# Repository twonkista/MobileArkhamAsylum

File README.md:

The Mobile Arkham Asylum is a hardware project that combines embedded systems with power electronics to make a literal cage for my phone so I can physically stay away from my phone. 

Such times inlude:
- study times
- bed

Features:
- 2 hour mode button (to lock for 2 hours)
- 8 hour mode button (to lock for 8 hours)
- I2C display (for time left and a generic clock)
- toggle button (to toggle the aformentioned stuff)

What I will bring:
- KiCad Schematic + footprint (done my g) (further improvements will be made like removing all voltage calculators im just gonna buy a voltimeter or steal one from someone)
- Arduino code (code done)
- Fusion 360 model

Full Plan + BOM

[BOM](https://docs.google.com/document/d/e/2PACX-1vQ0ssNzyhJEF3FpFiAyLGEXaUKHkRYoLOrRBAidYV5ManKBPaF_fq7NoqSav6IvK6zJQknT9mqp2-qP/pub) 

Picture of PCB (Render)

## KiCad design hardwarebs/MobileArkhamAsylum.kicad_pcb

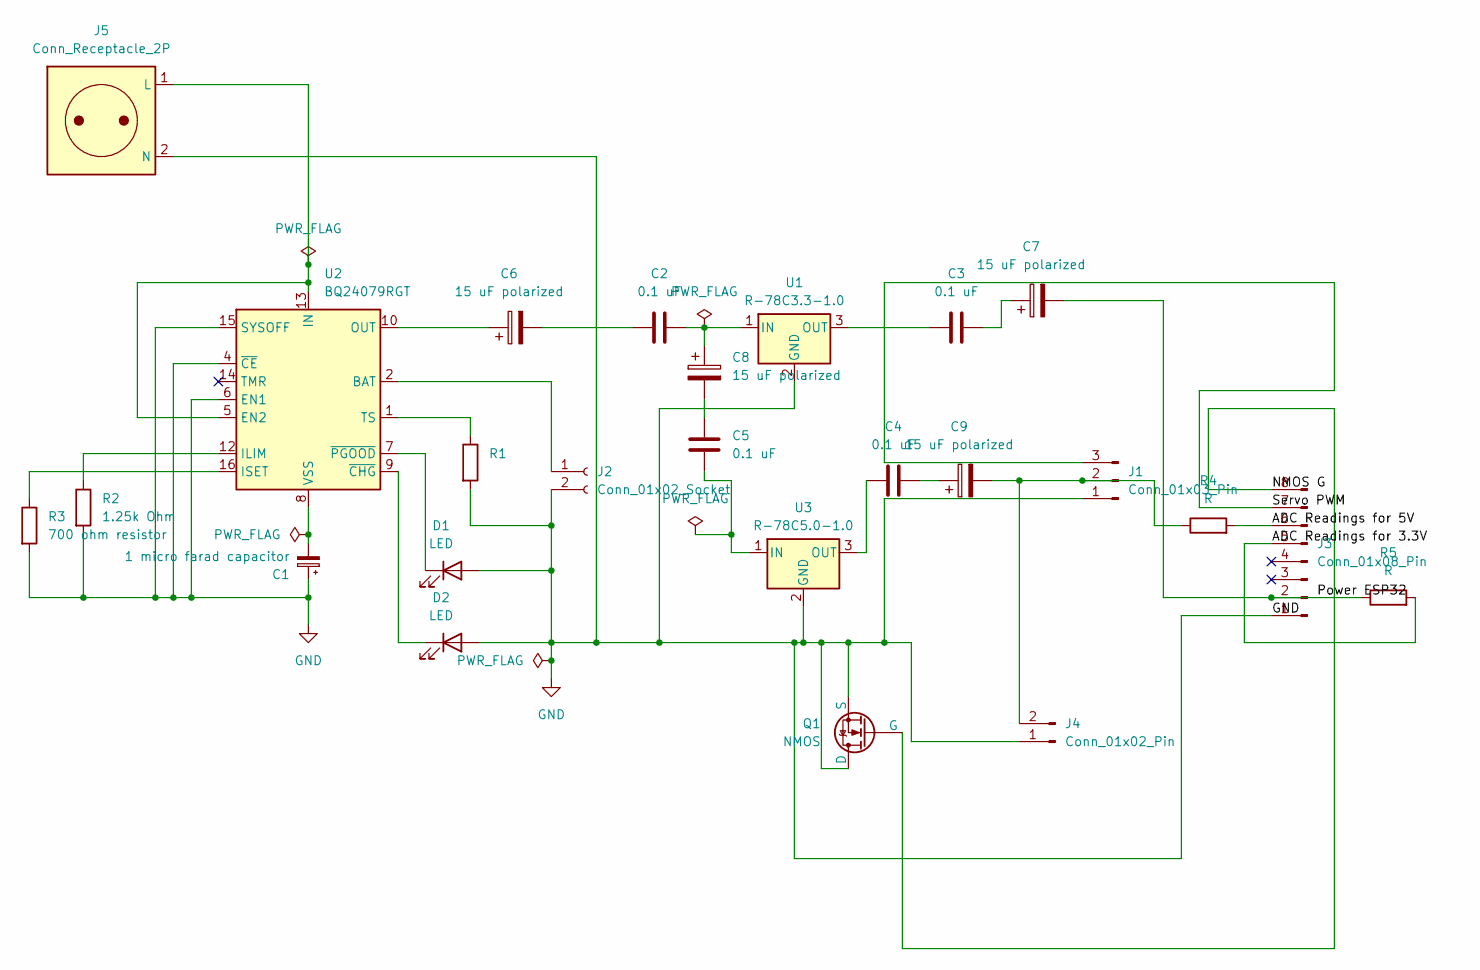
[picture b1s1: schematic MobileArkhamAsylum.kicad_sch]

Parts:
C1: 1 micro farad capacitor; CP_Radial_D5.0mm_P2.00mm
C2, C3, C4, C5: 0.1 uF; CP_Radial_D5.0mm_P2.50mm
C6, C7, C8, C9: 15 uF polarized; CP_Radial_D6.3mm_P2.50mm
D1, D2: LED; LED_D5.0mm
J1: Conn_01x03_Pin; PinHeader_1x03_P1.27mm_Vertical
J2: Conn_01x02_Socket; PinSocket_1x02_P1.27mm_Vertical
J3: Conn_01x08_Pin; PinHeader_1x08_P1.27mm_Vertical
J4: Conn_01x02_Pin; PinHeader_1x02_P1.27mm_Vertical
J5: Conn_Receptacle_2P; BarrelJack_CUI_PJ-063AH_Horizontal
Q1: NMOS; SOT-23
R1: 10k Ohms; R_Axial_DIN0204_L3.6mm_D1.6mm_P7.62mm_Horizontal
R2: 1.25k Ohm; R_Axial_DIN0204_L3.6mm_D1.6mm_P7.62mm_Horizontal
R3: 700 ohm resistor; R_Axial_DIN0204_L3.6mm_D1.6mm_P7.62mm_Horizontal
R4, R5: R; R_Axial_DIN0414_L11.9mm_D4.5mm_P5.08mm_Vertical
U1: R-78C3.3-1.0; Converter_DCDC_RECOM_R-78E-0.5_THT
U2: BQ24079RGT; VQFN-16-1EP_3x3mm_P0.5mm_EP1.6x1.6mm
U3: R-78C5.0-1.0; Converter_DCDC_RECOM_R-78E-0.5_THT

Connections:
/ADC Readings for 3.3V: J3.5, R5.2
/ADC Readings for 5V: J3.6, R4.2
/NMOS G: J3.8, Q1.2 (G)
/Power ESP32: C7.2, J3.2, R5.1
/Servo PWM: J1.3, J3.7
GND: C1.1, D1.2 (A), D2.2 (A), J1.1, J2.2, J3.1, J4.1, J5.2 (N), Q1.1 (D), Q1.3 (S), R1.2, R2.2, R3.2, U1.2 (GND), U2.4 (~CE), U2.6 (EN1), U2.15 (SYSOFF), U3.2 (GND)
unnamed: C1.2, U2.8 (VSS), U2.17 (VSS)
unnamed: C2.2, C6.2
unnamed: C3.1, C7.1
unnamed: C4.2, C9.1
unnamed: C5.1, C8.2
unnamed: C6.1, U2.10 (OUT), U2.11 (OUT)
unnamed: D1.1 (K), U2.7 (~PGOOD)
unnamed: D2.1 (K), U2.9 (~CHG)
unnamed: C9.2, J1.2, J4.2, R4.1
unnamed: J2.1, U2.2 (BAT), U2.3 (BAT)
unnamed: J5.1 (L), U2.5 (EN2), U2.13 (IN)
unnamed: C2.1, C8.1, U1.1 (IN)
unnamed: C3.2, U1.3 (OUT)
unnamed: R2.1, U2.12 (ILIM)
unnamed: R3.1, U2.16 (ISET)
unnamed: R1.1, U2.1 (TS)
unnamed: C5.2, U3.1 (IN)
unnamed: C4.1, U3.3 (OUT)

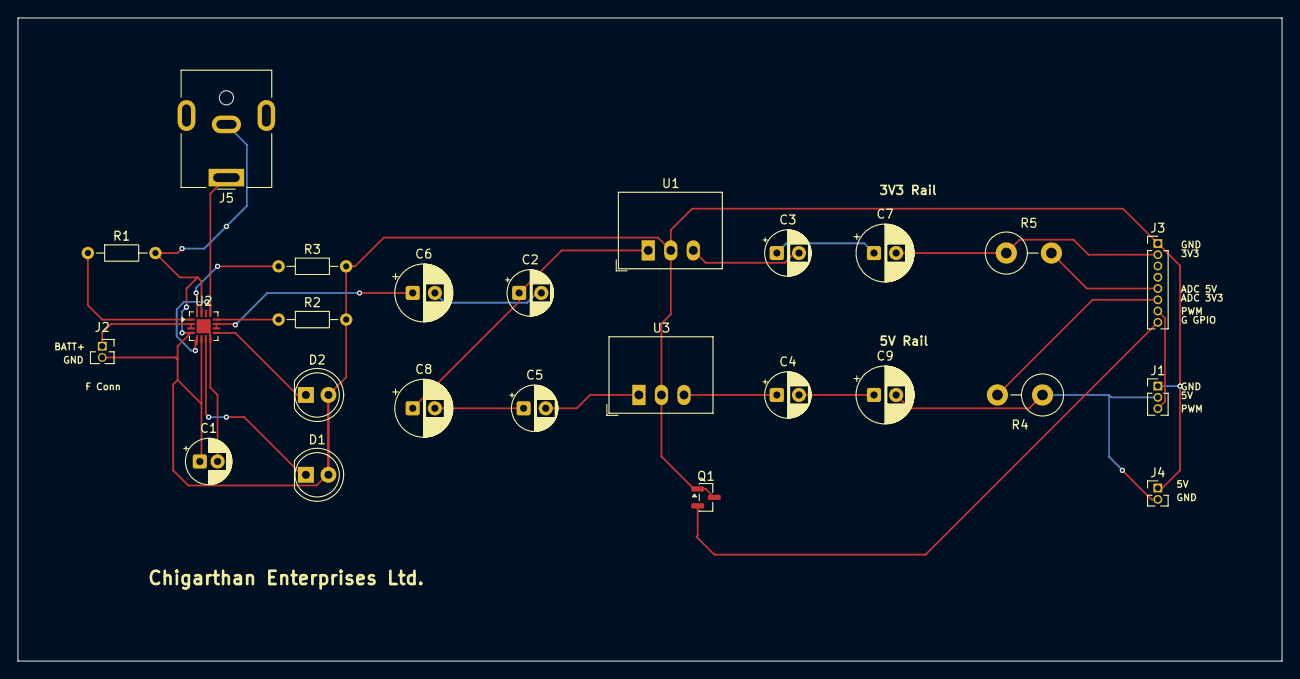
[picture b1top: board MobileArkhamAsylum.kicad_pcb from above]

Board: 2 copper layers, 142.5 x 72.5 mm, 25 parts (0 on the bottom side), 24 nets.

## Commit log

2026-01-15 ITS AN ESP32 I SWEAR GUYS I SWEAR I SWEAR ITS AN E
2026-01-15 things of that nature
    Add project description and features for Mobile Arkham Asylum.
2026-01-15 Update README with KiCad footprint and BOM link
    Added footprint to KiCad Schematic and updated BOM link.
2026-01-15 Update README with BOM link
2026-01-18 see i can deliver on promises
2026-01-18 hardwaregooner
2026-01-18 v2 footprint and design
2026-01-20 PCB V2 WITH SOME BOM EDITS
2026-01-26 Add PCB render images to README
    Added images of PCB renders to the README.
2026-02-13 CODEBS DONE
2026-02-13 Revise project status and future plans in README
    Updated README with completed tasks and future improvements.
